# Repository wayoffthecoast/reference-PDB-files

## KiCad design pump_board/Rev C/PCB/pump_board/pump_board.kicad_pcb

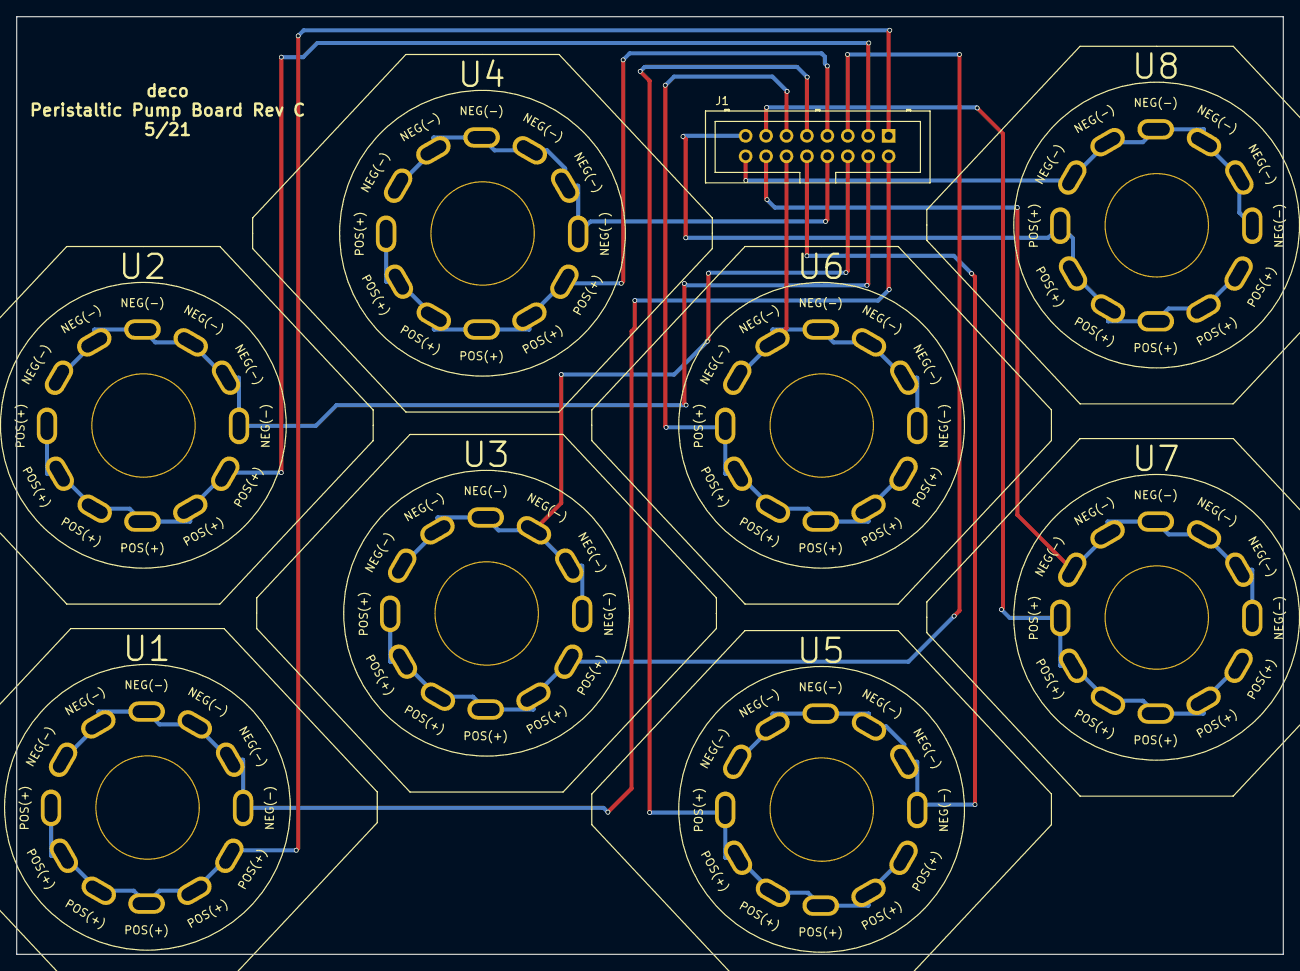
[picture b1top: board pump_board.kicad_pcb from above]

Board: 2 copper layers, 157.5 x 116.6 mm, 9 parts (0 on the bottom side), 16 nets.

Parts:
J1: Conn_02x08_Odd_Even; pump_2x8_connector
U1, U2, U3, U4, U5, U6, U7, U8: peristaltic_pump; peristlatic_pump_2020_04_29

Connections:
unnamed: J1.1, U1.1
unnamed: J1.2, U1.2
unnamed: J1.3, U2.1
unnamed: J1.4, U2.2
unnamed: J1.5, U3.1
unnamed: J1.6, U3.2
unnamed: J1.7, U4.1
unnamed: J1.8, U4.2
unnamed: J1.9, U5.1
unnamed: J1.10, U5.2
unnamed: J1.11, U6.1
unnamed: J1.12, U6.2
unnamed: J1.13, U7.1
unnamed: J1.14, U7.2
unnamed: J1.15, U8.1
unnamed: J1.16, U8.2
